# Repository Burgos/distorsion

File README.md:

Stupid audio processing project with
M4 cortex microprocessor

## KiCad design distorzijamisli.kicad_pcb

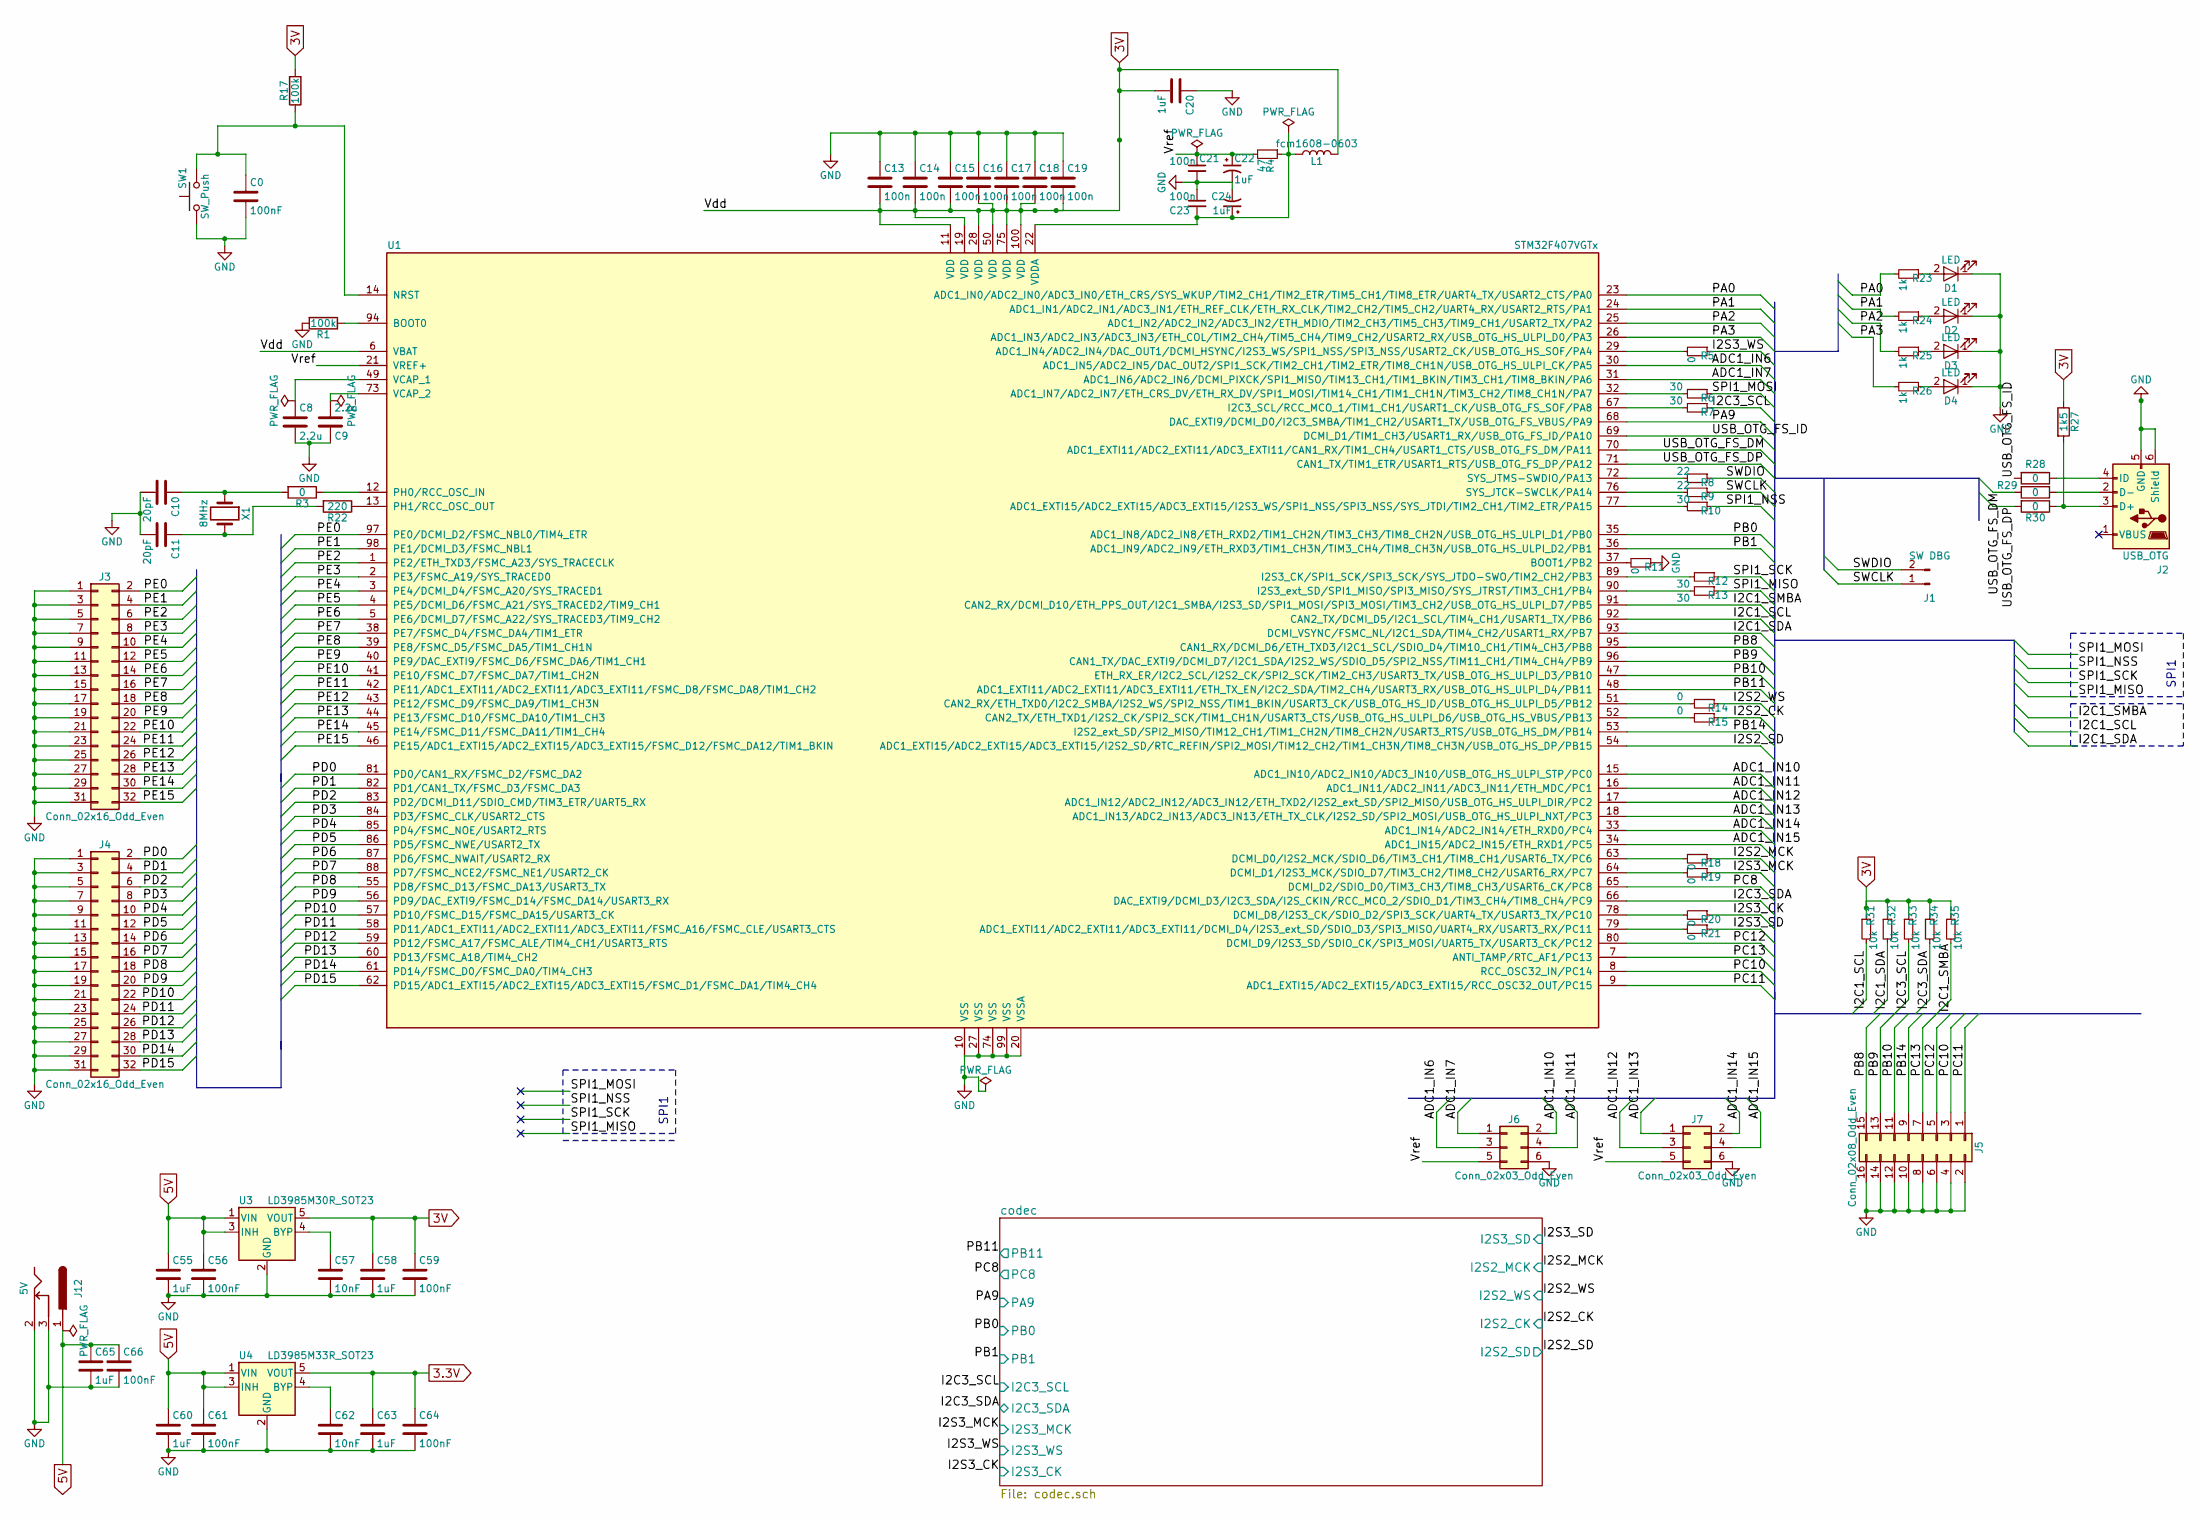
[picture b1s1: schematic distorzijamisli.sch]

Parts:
C0, C56, C59, C61, C64, C66: 100nF; C_0805_HandSoldering
C8, C9: 2.2u; C_0805_HandSoldering
C10, C11: 20pF; C_0805_HandSoldering
C13, C14, C15, C16, C17, C18, C19, C21, C23: 100n; C_0805_HandSoldering
C20, C22, C24, C55, C58, C60, C63, C65: 1uF; C_0805_HandSoldering
C57, C62: 10nF; C_0805_HandSoldering
D1, D2, D3, D4: LED; LED_0805_HandSoldering
J1: SW DBG; Pin_Header_Straight_1x02
J2: USB_OTG; USB_Mini-B
J3, J4: Conn_02x16_Odd_Even; Pin_Header_Straight_2x16
J5: Conn_02x08_Odd_Even; Pin_Header_Straight_2x08
J6, J7: Conn_02x03_Odd_Even; Pin_Header_Straight_2x03
J12: 5V; BARREL_JACK
L1: fcm1608-0603; L_0603_HandSoldering
R1, R17: 100k; R_0805_HandSoldering
R3, R5, R11, R14, R15, R18, R19, R20, R21, R28, R29, R30: 0; R_0805_HandSoldering
R4: 47; R_0805_HandSoldering
R6, R7, R10, R12, R13: 30; R_0805_HandSoldering
R8, R9: 22; R_0805_HandSoldering
R22: 220; R_0805_HandSoldering
R23, R24, R25, R26: 1k; R_0805_HandSoldering
R27: 1k5; R_0805_HandSoldering
R31, R32, R33, R34, R35: 10k; R_0805_HandSoldering
SW1: SW_Push; SW_PUSH_6mm
U1: STM32F407VGTx; LQFP-100_14x14mm_Pitch0.5mm
U3: LD3985M30R_SOT23; SOT-23-5_HandSoldering
U4: LD3985M33R_SOT23; SOT-23-5_HandSoldering
X1: 8MHz; HC-49V

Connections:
3.3V: C63.1, C64.1, U4.5 (VOUT); also elsewhere on the board
3V: C13.2, C14.2, C15.2, C16.2, C17.2, C18.2, C19.2, C20.2, C58.1, C59.1, L1.2, R17.2, R27.1, R31.1, R32.1, R33.1, R34.1, R35.1, U1.6 (VBAT), U1.11 (VDD), U1.19 (VDD), U1.28 (VDD), U1.50 (VDD), U1.75 (VDD), U1.100 (VDD), U3.5 (VOUT); also elsewhere on the board
5V: C55.1, C56.1, C60.1, C61.1, C65.1, C66.1, J12.1, U3.1 (VIN), U3.3 (INH), U4.1 (VIN), U4.3 (INH); also elsewhere on the board
/ADC1_IN6: J6.3, U1.30 (ADC1_IN5/ADC2_IN5/DAC_OUT2/SPI1_SCK/TIM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)
/ADC1_IN7: J6.1, U1.31 (ADC1_IN6/ADC2_IN6/DCMI_PIXCK/SPI1_MISO/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)
/ADC1_IN10: J6.2, U1.15 (ADC1_IN10/ADC2_IN10/ADC3_IN10/USB_OTG_H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)
/ADC1_IN11: J6.4, U1.16 (ADC1_IN11/ADC2_IN11/ADC3_IN11/ETH_MDC/P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)
/ADC1_IN12: J7.3, U1.17 (ADC1_IN12/ADC2_IN12/ADC3_IN12/ETH_TXD2/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)
/ADC1_IN13: J7.1, U1.18 (ADC1_IN13/ADC2_IN13/ADC3_IN13/ETH_TX_CL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)
/ADC1_IN14: J7.2, U1.33 (ADC1_IN14/ADC2_IN14/ETH_RXD0/PC4)
/ADC1_IN15: J7.4, U1.34 (ADC1_IN15/ADC2_IN15/ETH_RXD1/PC5)
/I2C1_SCL: R31.2, U1.92 (CAN2_TX/DCMI_D5/I2C1_SCL/TIM4_CH1/USART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)
/I2C1_SDA: R32.2, U1.93 (DCMI_VSYNC/FSMC_NL/I2C1_SDA/TIM4_CH2/US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)
/I2C1_SMBA: R35.2, U1.91 (CAN2_RX/DCMI_D10/ETH_PPS_OUT/I2C1_SMBA/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)
/I2C3_SCL: R7.1, R33.2; also elsewhere on the board
/I2C3_SDA: R34.2, U1.66 (DAC_EXTI9/DCMI_D3/I2C3_SDA/I2S_CKIN/RCC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); also elsewhere on the board
/I2S2_CK: R15.1; also elsewhere on the board
/I2S2_MCK: R18.1; also elsewhere on the board
/I2S2_SD: U1.54 (ADC1_EXTI15/ADC2_EXTI15/ADC3_EXTI15/I2S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); also elsewhere on the board
/I2S2_WS: R14.1; also elsewhere on the board
/I2S3_CK: R20.1; also elsewhere on the board
/I2S3_MCK: R19.1; also elsewhere on the board
/I2S3_SD: R21.1; also elsewhere on the board
/I2S3_WS: R5.1; also elsewhere on the board
/PA0: R23.2, U1.23 (ADC1_IN0/ADC2_IN0/ADC3_IN0/ETH_CRS/SYS_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)
/PA1: R24.2, U1.24 (ADC1_IN1/ADC2_IN1/ADC3_IN1/ETH_REF_CLK/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)
/PA2: R25.2, U1.25 (ADC1_IN2/ADC2_IN2/ADC3_IN2/ETH_MDIO/TIM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)
/PA3: R26.2, U1.26 (ADC1_IN3/ADC2_IN3/ADC3_IN3/ETH_COL/TIM2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)
/PA9: U1.68 (DAC_EXTI9/DCMI_D0/I2C3_SMBA/TIM1_CH2/US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); also elsewhere on the board
/PB0: U1.35 (ADC1_IN8/ADC2_IN8/ETH_RXD2/TIM1_CH2N/TI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); also elsewhere on the board
/PB1: U1.36 (ADC1_IN9/ADC2_IN9/ETH_RXD3/TIM1_CH3N/TI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); also elsewhere on the board
/PB8: J5.15, U1.95 (CAN1_RX/DCMI_D6/ETH_TXD3/I2C1_SCL/SDIO_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)
/PB9: J5.13, U1.96 (CAN1_TX/DAC_EXTI9/DCMI_D7/I2C1_SDA/I2S2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)
/PB10: J5.11, U1.47 (ETH_RX_ER/I2C2_SCL/I2S2_CK/SPI2_SCK/TIM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)
/PB11: U1.48 (ADC1_EXTI11/ADC2_EXTI11/ADC3_EXTI11/ETH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); also elsewhere on the board
/PB14: J5.9, U1.53 (I2S2_ext_SD/SPI2_MISO/TIM12_CH1/TIM1_CH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)
/PC8: U1.65 (DCMI_D2/SDIO_D0/TIM3_CH3/TIM8_CH3/USART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); also elsewhere on the board
/PC10: J5.3, U1.8 (RCC_OSC32_IN/PC14)
/PC11: J5.1, U1.9 (ADC1_EXTI15/ADC2_EXTI15/ADC3_EXTI15/RCC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)
/PC12: J5.5, U1.80 (DCMI_D9/I2S3_SD/SDIO_CK/SPI3_MOSI/UART5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)
/PC13: J5.7, U1.7 (ANTI_TAMP/RTC_AF1/PC13)
/PD0: J4.2, U1.81 (PD0/CAN1_RX/FSMC_D2/FSMC_DA2)
/PD1: J4.4, U1.82 (PD1/CAN1_TX/FSMC_D3/FSMC_DA3)
/PD2: J4.6, U1.83 (PD2/DCMI_D11/SDIO_CMD/TIM3_ETR/UART5_RX)
/PD3: J4.8, U1.84 (PD3/FSMC_CLK/USART2_CTS)
/PD4: J4.10, U1.85 (PD4/FSMC_NOE/USART2_RTS)
/PD5: J4.12, U1.86 (PD5/FSMC_NWE/USART2_TX)
/PD6: J4.14, U1.87 (PD6/FSMC_NWAIT/USART2_RX)
/PD7: J4.16, U1.88 (PD7/FSMC_NCE2/FSMC_NE1/USART2_CK)
/PD8: J4.18, U1.55 (PD8/FSMC_D13/FSMC_DA13/USART3_TX)
/PD9: J4.20, U1.56 (PD9/DAC_EXTI9/FSMC_D14/FSMC_DA14/USART3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)
/PD10: J4.22, U1.57 (PD10/FSMC_D15/FSMC_DA15/USART3_CK)
/PD11: J4.24, U1.58 (PD11/ADC1_EXTI11/ADC2_EXTI11/ADC3_EXTI1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)
/PD12: J4.26, U1.59 (PD12/FSMC_A17/FSMC_ALE/TIM4_CH1/USART3_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)
/PD13: J4.28, U1.60 (PD13/FSMC_A18/TIM4_CH2)
/PD14: J4.30, U1.61 (PD14/FSMC_D0/FSMC_DA0/TIM4_CH3)
/PD15: J4.32, U1.62 (PD15/ADC1_EXTI15/ADC2_EXTI15/ADC3_EXTI1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)
/PE0: J3.2, U1.97 (PE0/DCMI_D2/FSMC_NBL0/TIM4_ETR)
/PE1: J3.4, U1.98 (PE1/DCMI_D3/FSMC_NBL1)
/PE2: J3.6, U1.1 (PE2/ETH_TXD3/FSMC_A23/SYS_TRACECLK)
/PE3: J3.8, U1.2 (PE3/FSMC_A19/SYS_TRACED0)
/PE4: J3.10, U1.3 (PE4/DCMI_D4/FSMC_A20/SYS_TRACED1)
/PE5: J3.12, U1.4 (PE5/DCMI_D6/FSMC_A21/SYS_TRACED2/TIM9_C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)
/PE6: J3.14, U1.5 (PE6/DCMI_D7/FSMC_A22/SYS_TRACED3/TIM9_C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)
/PE7: J3.16, U1.38 (PE7/FSMC_D4/FSMC_DA4/TIM1_ETR)
/PE8: J3.18, U1.39 (PE8/FSMC_D5/FSMC_DA5/TIM1_CH1N)
/PE9: J3.20, U1.40 (PE9/DAC_EXTI9/FSMC_D6/FSMC_DA6/TIM1_CH1)
/PE10: J3.22, U1.41 (PE10/FSMC_D7/FSMC_DA7/TIM1_CH2N)
/PE11: J3.24, U1.42 (PE11/ADC1_EXTI11/ADC2_EXTI11/ADC3_EXTI1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)
/PE12: J3.26, U1.43 (PE12/FSMC_D9/FSMC_DA9/TIM1_CH3N)
/PE13: J3.28, U1.44 (PE13/FSMC_D10/FSMC_DA10/TIM1_CH3)
/PE14: J3.30, U1.45 (PE14/FSMC_D11/FSMC_DA11/TIM1_CH4)
/PE15: J3.32, U1.46 (PE15/ADC1_EXTI15/ADC2_EXTI15/ADC3_EXTI1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)
/SPI1_MISO: R13.1
/SPI1_MOSI: R6.1
/SPI1_NSS: R10.1
/SPI1_SCK: R12.1
/SWCLK: J1.1, R9.1
/SWDIO: J1.2, R8.1
/USB_OTG_FS_DM: R29.2, U1.70 (ADC1_EXTI11/ADC2_EXTI11/ADC3_EXTI11/CAN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)
/USB_OTG_FS_DP: R30.2, U1.71 (CAN1_TX/TIM1_ETR/USART1_RTS/USB_OTG_FS_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)
/USB_OTG_FS_ID: R28.2, U1.69 (DCMI_D1/TIM1_CH3/USART1_RX/USB_OTG_FS_I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)
/Vref: C21.1, C22.1, J6.5, J7.5, R4.2, U1.21 (VREF+)
GND: C0.2, C8.2, C9.1, C10.2, C11.2, C13.1, C14.1, C15.1, C16.1, C17.1, C18.1, C19.1, C20.1, C21.2, C22.2, C23.1, C24.2, C55.2, C56.2, C57.2, C58.2, C59.2, C60.2, C61.2, C62.2, C63.2, C64.2, C65.2, C66.2, D1.1 (K), D2.1 (K), D3.1 (K), D4.1 (K), J2.5 (GND), J2.6 (Shield), J3.1, J3.3, J3.5, J3.7, J3.9, J3.11, J3.13, J3.15, J3.17, J3.19, J3.21, J3.23, J3.25, J3.27, J3.29, J3.31, J4.1, J4.3, J4.5, J4.7, J4.9, J4.11, J4.13, J4.15, J4.17, J4.19, J4.21, J4.23, J4.25, J4.27, J4.29, J4.31, J5.2, J5.4, J5.6, J5.8, J5.10, J5.12, J5.14, J5.16, J6.6, J7.6, J12.2, J12.3, R1.2, R11.1, SW1.1, U1.10 (VSS), U1.20 (VSSA), U1.27 (VSS), U1.74 (VSS), U1.99 (VSS), U3.2 (GND), U4.2 (GND); also elsewhere on the board
unnamed: C0.1, R17.1, SW1.2, U1.14 (NRST)
unnamed: C8.1, U1.49 (VCAP_1)
unnamed: C9.2, U1.73 (VCAP_2)
unnamed: C10.1, R3.2, X1.1
unnamed: C11.1, R22.2, X1.2
unnamed: C23.2, C24.1, L1.1, R4.1, U1.22 (VDDA)
unnamed: C57.1, U3.4 (BYP)
unnamed: C62.1, U4.4 (BYP)
unnamed: D1.2 (A), R23.1
unnamed: D2.2 (A), R24.1
unnamed: D3.2 (A), R25.1
unnamed: D4.2 (A), R26.1
unnamed: J2.2 (D-), R29.1
unnamed: J2.3 (D+), R27.2, R30.1
unnamed: J2.4 (ID), R28.1
unnamed: R1.1, U1.94 (BOOT0)
unnamed: R3.1, U1.12 (PH0/RCC_OSC_IN)
unnamed: R5.2, U1.29 (ADC1_IN4/ADC2_IN4/DAC_OUT1/DCMI_HSYNC/I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)
unnamed: R6.2, U1.32 (ADC1_IN7/ADC2_IN7/ETH_CRS_DV/ETH_RX_DV/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)
unnamed: R7.2, U1.67 (I2C3_SCL/RCC_MCO_1/TIM1_CH1/USART1_CK/U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)
unnamed: R8.2, U1.72 (SYS_JTMS-SWDIO/PA13)
unnamed: R9.2, U1.76 (SYS_JTCK-SWCLK/PA14)
unnamed: R10.2, U1.77 (ADC1_EXTI15/ADC2_EXTI15/ADC3_EXTI15/I2S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)
unnamed: R11.2, U1.37 (BOOT1/PB2)
unnamed: R12.2, U1.89 (I2S3_CK/SPI1_SCK/SPI3_SCK/SYS_JTDO-SWO/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)
unnamed: R13.2, U1.90 (I2S3_ext_SD/SPI1_MISO/SPI3_MISO/SYS_JTR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)
unnamed: R14.2, U1.51 (CAN2_RX/ETH_TXD0/I2C2_SMBA/I2S2_WS/SPI2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)
unnamed: R15.2, U1.52 (CAN2_TX/ETH_TXD1/I2S2_CK/SPI2_SCK/TIM1_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)
unnamed: R18.2, U1.63 (DCMI_D0/I2S2_MCK/SDIO_D6/TIM3_CH1/TIM8_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)
unnamed: R19.2, U1.64 (DCMI_D1/I2S3_MCK/SDIO_D7/TIM3_CH2/TIM8_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)
unnamed: R20.2, U1.78 (DCMI_D8/I2S3_CK/SDIO_D2/SPI3_SCK/UART4_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)
unnamed: R21.2, U1.79 (ADC1_EXTI11/ADC2_EXTI11/ADC3_EXTI11/DCM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)
unnamed: R22.1, U1.13 (PH1/RCC_OSC_OUT)

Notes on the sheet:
SPI1

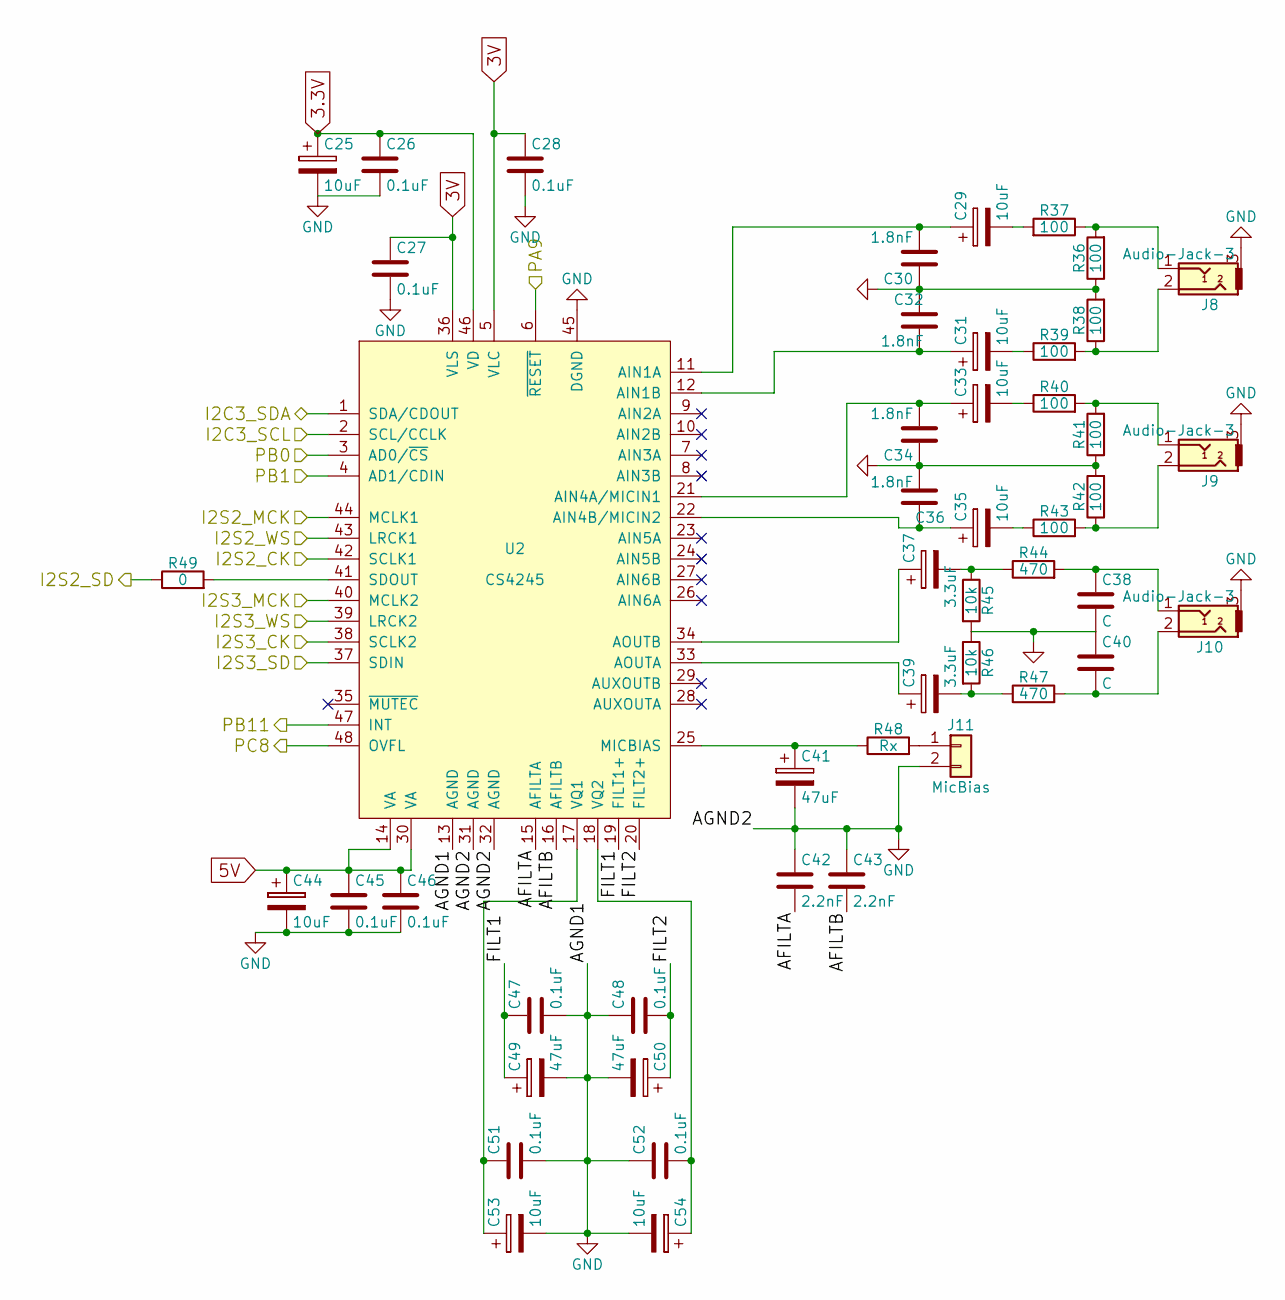
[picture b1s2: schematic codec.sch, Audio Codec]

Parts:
C25, C29, C31, C33, C35, C44, C53: 10uF; c_elec_4x4.5
C26, C27, C28, C45, C46, C47, C48, C51, C52: 0.1uF; C_0805_HandSoldering
C30, C32, C34, C36: 1.8nF; C_0805_HandSoldering
C37, C39: 3.3uF; c_elec_4x4.5
C38, C40: C; C_0805_HandSoldering
C41, C49, C50: 47uF; c_elec_6.3x7.7
C42, C43: 2.2nF; C_0805_HandSoldering
C54: 10uF; C_2225_HandSoldering
J8, J9, J10: Audio-Jack-3; PJ311_3.5mm_Jack
J11: MicBias; Pin_Header_Straight_1x02
R36, R37, R38, R39, R40, R41, R42, R43: 100; R_0805_HandSoldering
R44, R47: 470; R_0805_HandSoldering
R45, R46: 10k; R_0805_HandSoldering
R48: Rx; R_0805_HandSoldering
R49: 0; R_0805_HandSoldering
U2: CS4245; LQFP-48_7x7mm_Pitch0.5mm

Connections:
3.3V: C25.1, C26.1, U2.46 (VD); also elsewhere on the board
3V: C27.1, C28.1, U2.5 (VLC), U2.36 (VLS); also elsewhere on the board
5V: C44.1, C45.1, C46.1, U2.14 (VA), U2.30 (VA); also elsewhere on the board
/I2C3_SCL: U2.2 (SCL/CCLK); also elsewhere on the board
/I2C3_SDA: U2.1 (SDA/CDOUT); also elsewhere on the board
/I2S2_CK: U2.42 (SCLK1); also elsewhere on the board
/I2S2_MCK: U2.44 (MCLK1); also elsewhere on the board
/I2S2_SD: R49.1; also elsewhere on the board
/I2S2_WS: U2.43 (LRCK1); also elsewhere on the board
/I2S3_CK: U2.38 (SCLK2); also elsewhere on the board
/I2S3_MCK: U2.40 (MCLK2); also elsewhere on the board
/I2S3_SD: U2.37 (SDIN); also elsewhere on the board
/I2S3_WS: U2.39 (LRCK2); also elsewhere on the board
/PA9: U2.6 (~RESET); also elsewhere on the board
/PB0: U2.3 (AD0/~CS); also elsewhere on the board
/PB1: U2.4 (AD1/CDIN); also elsewhere on the board
/PB11: U2.47 (INT); also elsewhere on the board
/PC8: U2.48 (OVFL); also elsewhere on the board
/codec/AFILTA: C42.2, U2.15 (AFILTA)
/codec/AFILTB: C43.2, U2.16 (AFILTB)
/codec/FILT1: C47.1, C49.1, U2.19 (FILT1+)
/codec/FILT2: C48.2, C50.1, U2.20 (FILT2+)
GND: C25.2, C26.2, C27.2, C28.2, C30.1, C32.1, C34.1, C36.2, C38.2, C40.1, C41.2, C42.1, C43.1, C44.2, C45.2, C46.2, C47.2, C48.1, C49.2, C50.2, C51.2, C52.1, C53.2, C54.2, J8.3, J9.3, J10.3, J11.2, R36.1, R38.2, R41.1, R42.2, R45.2, R46.1, U2.13 (AGND), U2.31 (AGND), U2.32 (AGND), U2.45 (DGND); also elsewhere on the board
unnamed: C29.1, C30.2, U2.11 (AIN1A)
unnamed: C29.2, R37.2
unnamed: C31.1, C32.2, U2.12 (AIN1B)
unnamed: C31.2, R39.1
unnamed: C33.1, C34.2, U2.21 (AIN4A/MICIN1)
unnamed: C33.2, R40.1
unnamed: C35.1, C36.1, U2.22 (AIN4B/MICIN2)
unnamed: C35.2, R43.1
unnamed: C37.1, U2.34 (AOUTB)
unnamed: C37.2, R44.1, R45.1
unnamed: C38.1, J10.1, R44.2
unnamed: C39.1, U2.33 (AOUTA)
unnamed: C39.2, R46.2, R47.1
unnamed: C40.2, J10.2, R47.2
unnamed: C41.1, R48.1, U2.25 (MICBIAS)
unnamed: C51.1, C53.1, U2.17 (VQ1)
unnamed: C52.2, C54.1, U2.18 (VQ2)
unnamed: J8.1, R36.2, R37.1
unnamed: J8.2, R38.1, R39.2
unnamed: J9.1, R40.2, R41.2
unnamed: J9.2, R42.1, R43.2
unnamed: J11.1, R48.2
unnamed: R49.2, U2.41 (SDOUT)

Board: 2 copper layers, 129 parts (0 on the bottom side), 140 nets, no tracks yet.

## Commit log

2017-11-08 Initial commit
    ERC is passing, we have the basic layout, usb, sw connectors,
    bypasses, GPIO connectors and ADC1 connector.
2017-11-08 Add git ignore
2017-11-08 Add readme
2017-11-09 Add codec subsheet
    This adds the subsheet with the CS4245 audio codec
    connected to the main processor.
2017-11-09 [codec] Sort the input filters and add comp. values
    The input filter schematic was wrong, it was using the
    output's LP filter circuit (copy/paste error). All components
    now have values, as per CS4245's datasheet.
2017-11-22 Add power regulators with 5, 3 and 3.3V.
    In addition, the connector is now as short as needed.
2017-11-22 Unignore .lib files as we're going to add cache
2017-11-22 Add cache library file
2017-11-22 Move the I2S2_SD termination resistor to driver
2017-12-05 Set values to components and minor fixes.
2017-12-05 Termination resistors
2017-12-05 Add some of the pinouts
2017-12-06 Add remaining footprints
2017-12-06 Initial placement of the components on PCB
    just using auto spread-around
2017-12-09 Connect Vbat directly to Vdd
2017-12-09 Regenerate netlist
2017-12-09 Regenerated footprints for the new netlist
2017-12-09 Remove several port connectors from the board
    As they take too much space, with the sparse pin
    layout, we'll just remove them, as they have no use in this
    application.
